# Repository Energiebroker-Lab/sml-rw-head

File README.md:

# sml-rw-head

## Overview

**sml-rw-head** is a versatile read-write module designed to attach to power meters via a magnet.
It reads the SML (Smart Message Language) or ODT stream from the D0 interface of the meter.
Additionally, the device is equipped to send pulses for entering the PIN or navigating through the menu of the meter
and for example toggle the info mode.

This project encompasses three main components:

1. **Hardware:** Includes schematics and PCB (Printed Circuit Board) designs.
2. **3D-Printable Parts:** Consists of printable components that complement the hardware.
3. **Code:** The code is an implementation example
of the sml-rw-head device.

Each major component has its dedicated directory with its own README.md for detailed information.

## Project Structure

- **Hardware:** The hardware files are located in the `./hardware/d0reader` subdirectory. Refer to the [Hardware README](./hardware/d0reader/README.md) for specifics.

- **3D-Printable Parts:** Find 3D-printable files in the `./hardware/3d-print` subdirectory. More details are available in the [3D-Print README](./hardware/3d-print/README.md).

- **Code:** The source code is in the `./code/sml_rw` subdirectory. To get started with the code, please check the [Code README](./code/sml_rw/README.md).

## Usage

Before using the sml-rw-head module, make sure to review the documentation for each component. Follow the guidelines provided in the respective READMEs for successful integration into your project.

### Preparation
Before using the sml-rw-head module, you need to configure the device using the `ftprog_template.xml` file. Import the file and perform the configuration using the [ftprog](https://ftdichip.com/utilities/) software supplied by FTDI.

## Contributions

Contributions to the sml-rw-head project are welcome! If you have ideas, improvements, or bug fixes, please feel free to submit issues or pull requests.

## License

This project is licensed under the [MIT License](LICENSE). See the LICENSE file for more details.

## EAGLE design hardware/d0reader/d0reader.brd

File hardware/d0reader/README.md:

Based on https://www.stefan-weigert.de/php_loader/sml.php

# BOM
| Part | Value           | Device             | Package             | Description                                                             |
|------|-----------------|--------------------|---------------------|-------------------------------------------------------------------------|
| C1   | 100n            | Capacitor          | 0805                | Capacitor, Ceramic                                                      |
| C2   | 100n            | Capacitor          | 0805                | Capacitor, Ceramic                                                      |
| C3   | 100n            | Capacitor          | 0805                | Capacitor, Ceramic                                                      |
| C4   | 1u              | Capacitor          | 0805                | Capacitor, Ceramic                                                      |
| C5   | 1u              | Capacitor          | 0805                | Capacitor, Ceramic                                                      |
| C6   | 22u             | EEEHA1C220R        | CPOL-EU153CLV-0505  | 153CLV-0505 POLARIZED CAPACITOR                                         |
| IC1  | FT232RL         | FT232RL            | SSOP28              | Source: http://www.ftdichip.com/Documents/DataSheets/DS_FT232R_v104.pdf | 
| LED1 | KCL5587S        | LED5MM             | LED5MM              | Infrared-Emitter                                                        |                                                                     
| LED2 | LEDCHIPLED_0805 | CHIPLED            | 0805                | LED (optional)                                                          |                                                                                        
| LED3 | LEDCHIPLED_0805 | CHIPLED            | 0805                | LED (optional)                                                          |                                                                                        
| PAD1 |                 | WIREPADSMD1,27-254 | SMD1,27-2,54        | Wire PAD connect wire on PCB                                            |                                            
| PAD2 |                 | WIREPADSMD1,27-254 | SMD1,27-2,54        | Wire PAD connect wire on PCB                                            |                                        
| PAD3 |                 | WIREPADSMD1,27-254 | SMD1,27-2,54        | Wire PAD connect wire on PCB                                            |                           
| PAD4 |                 | WIREPADSMD1,27-254 | SMD1,27-2,54        | Wire PAD connect wire on PCB                                            |                           
| Q1   | BC817           | BC817-16LT1SMD     | SOT23-BEC           | NPN Transistor                                                          |     NPN Transistor                                                      |                
| Q2   | SFH_309_FA-4/5  | SFH_309_FA-4/5     | XDCR_SFH_309_FA-4/5 | Phototransistor IR Chip Silicon 900nm 2-Pin T-1 Check prices            |
| Q3   | BC817           | BC817-16LT1SMD     | SOT23-BEC           | NPN Transistor                                                          |                                            
| Q4   | BC817           | BC817-16LT1SMD     | SOT23-BEC           | NPN Transistor                                                          |                                           
| R1   | 220             | Resistor           | 0805                | Resistor                                                                |
| R2   | 220             | Resistor           | 0805                | Resistor                                                                |                                     
| R3   | 12k             | Resistor           | 0805                | Resistor                                                                |                                     
| R4   | 12k             | Resistor           | 0805                | Resistor                                                                |                                     
| R5   | 75              | Resistor           | 0805                | Resistor                                                                |                                     
| R6   | 220             | Resistor           | 0805                | Resistor                                                                |                                     
| R7   | 220             | Resistor           | 0805                | Resistor                                                                |                                     
| U4   | SN74LVC1G17DBVR | Schmitt-Trigger    | SOT-23              | Schmitt-Trigger                                                         |

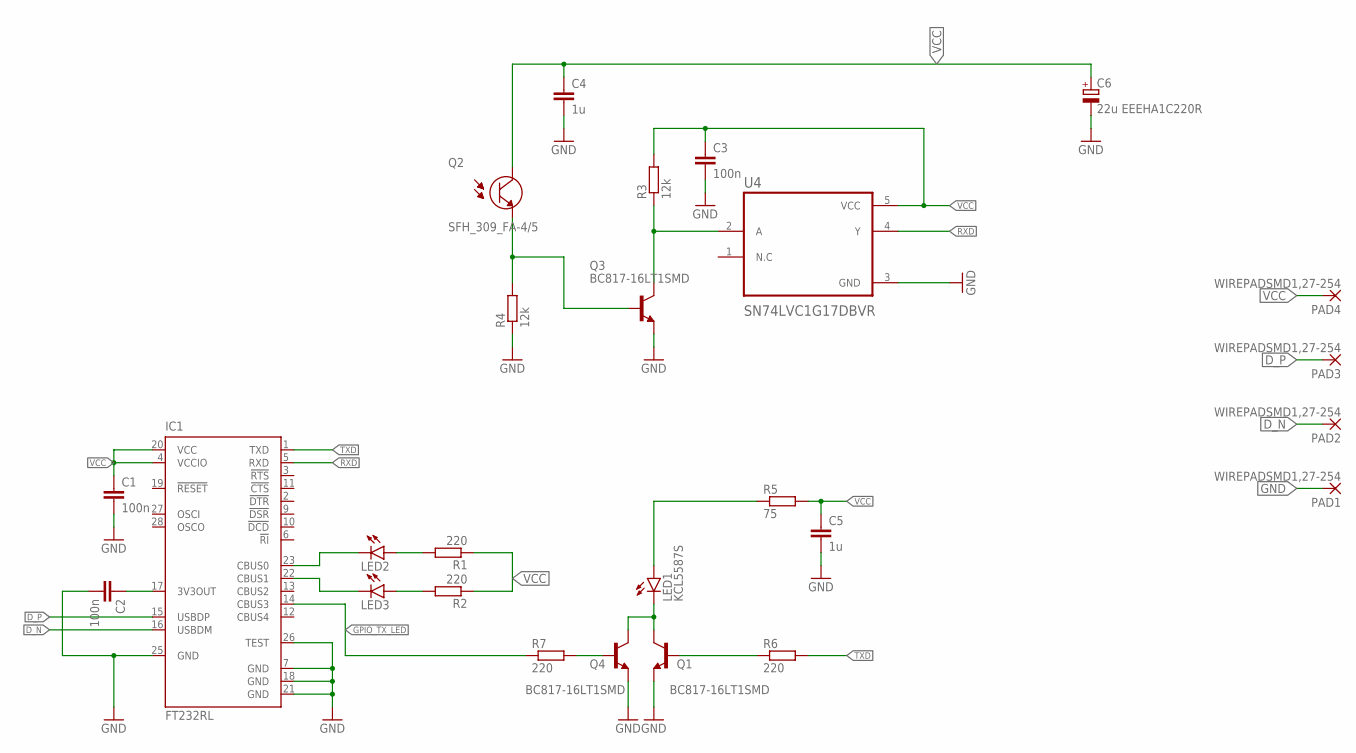
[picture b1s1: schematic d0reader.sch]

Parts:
C1, C2, C3: 100n; C0805
C4, C5: 1u; C0805
C6: 22u EEEHA1C220R; 153CLV-0505
IC1: FT232RL; SSOP28
LED1: KCL5587S; LED5MM
LED2, LED3: LEDCHIPLED_0805; CHIPLED_0805
PAD1, PAD2, PAD3, PAD4: WIREPADSMD1,27-254; SMD1,27-2,54
Q1, Q3, Q4: BC817-16LT1SMD; SOT23-BEC
Q2: SFH_309_FA-4/5; XDCR_SFH_309_FA-4/5
R1, R2, R6, R7: 220; R0805
R3, R4: 12k; R0805
R5: 75; R0805
U4: SN74LVC1G17DBVR; SOT95P280X145-5N

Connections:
D_N: IC1.16 (USBDM), PAD2.1
D_P: IC1.15 (USBDP), PAD3.1
GND: C1.2, C2.2, C3.2, C4.2, C5.2, C6.-, IC1.7 (GND), IC1.18 (GND), IC1.21 (GND), IC1.25 (GND), IC1.26 (TEST), PAD1.1, Q1.E, Q3.E, Q4.E, R4.1, U4.3 (GND)
GPIO_TX_LED: IC1.14 (CBUS3), R7.1
INPUTA: Q3.C, R3.1, U4.2 (A)
unnamed: LED2.A, R1.2
unnamed: LED3.A, R2.2
unnamed: C2.1, IC1.17 (3V3OUT)
OPTO_RX: Q2.1 (E), Q3.B, R4.2
RXD: IC1.5 (RXD), U4.4 (Y)
RXLED: IC1.22 (CBUS1), LED3.C
TXD: IC1.1 (TXD), R6.2
TXLED: IC1.23 (CBUS0), LED2.C
TXLEDGND: LED1.K (C), Q1.C, Q4.C
TXLEDVCC: LED1.A, R5.1
TX_LED_Q1: Q1.B, R6.1
TX_LED_Q4: Q4.B, R7.2
VCC: C1.1, C3.1, C4.1, C5.1, C6.+, IC1.4 (VCCIO), IC1.20 (VCC), PAD4.1, Q2.2 (C), R1.1, R2.1, R3.2, R5.2, U4.5 (VCC)

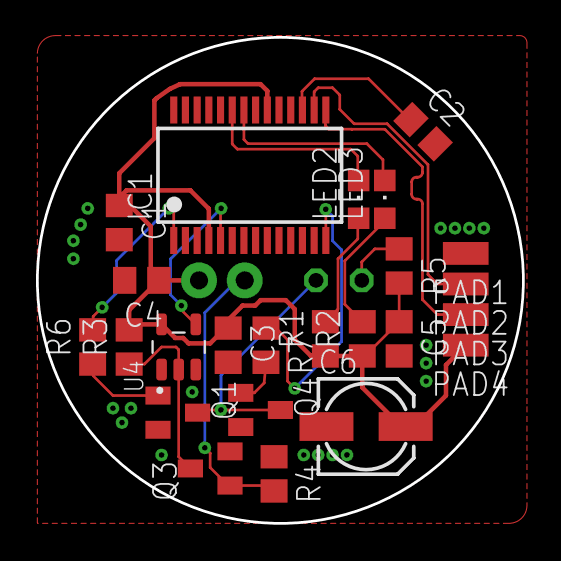
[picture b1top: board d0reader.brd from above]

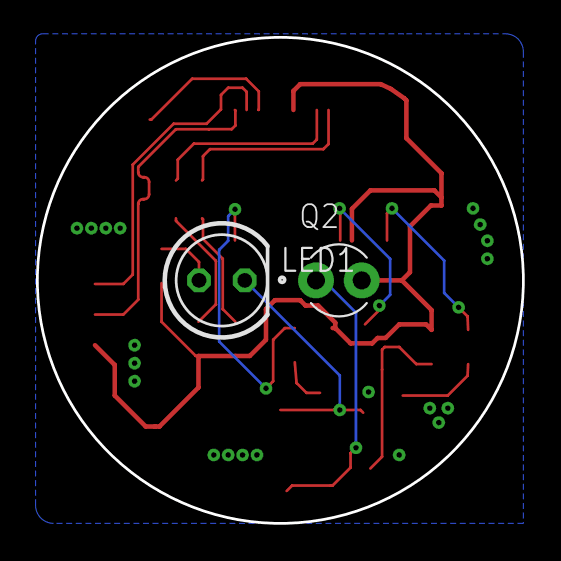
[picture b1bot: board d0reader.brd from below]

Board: 2 copper layers, 27.0 x 27.0 mm, 26 parts (2 on the bottom side), 18 nets.

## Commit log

2023-12-19 adds hardware
2023-12-19 updates .gitignore
2023-12-21 adds git action workflow pylint, mypy
2023-12-21 code push
2023-12-21 updates pylint git action workflow
2023-12-21 updates mypy git action workflow
2023-12-21 adds pylintrc
2023-12-21 updates pylintrc encoding
2023-12-21 updates pylintrc
2023-12-22 adds dd3 odt and 2way
2023-12-22 adds reattach pre port open
2023-12-22 adds odt logic
2023-12-22 adds README.md
2023-12-22 example code
    code push
2024-01-02 adds easy meter handler
2024-01-02 updates README.md for the code
2024-01-02 updates README.md for depth stencil
2024-01-02 updates README.md for hardware
2024-01-02 Create LICENSE
2024-01-02 updates README.md for project
2024-01-02 adds ftprog template
2024-01-02 adds image to README.md
2024-01-02 Bump actions/setup-python from 2 to 5
    Bumps [actions/setup-python](https://github.com/actions/setup-python) from 2 to 5.
    - [Release notes](https://github.com/actions/setup-python/releases)
    - [Commits](https://github.com/actions/setup-python/compare/v2...v5)
    ---
    updated-dependencies:
    - dependency-name: actions/setup-python
2024-01-02 Bump actions/checkout from 2 to 4
    Bumps [actions/checkout](https://github.com/actions/checkout) from 2 to 4.
    - [Release notes](https://github.com/actions/checkout/releases)
    - [Changelog](https://github.com/actions/checkout/blob/main/CHANGELOG.md)
    - [Commits](https://github.com/actions/checkout/compare/v2...v4)
    ---
    updated-dependencies:
2024-01-02 removes wrong name from README.md
2024-04-01 Bump fire from 0.5.0 to 0.6.0 in /code/sml_rw
    Bumps [fire](https://github.com/google/python-fire) from 0.5.0 to 0.6.0.
    - [Release notes](https://github.com/google/python-fire/releases)
    - [Commits](https://github.com/google/python-fire/compare/v0.5.0...v0.6.0)
    ---
    updated-dependencies:
    - dependency-name: fire
2024-05-01 Bump smllib from 1.3 to 1.4 in /code/sml_rw
    Bumps [smllib](https://github.com/spacemanspiff2007/SmlLib) from 1.3 to 1.4.
    - [Release notes](https://github.com/spacemanspiff2007/SmlLib/releases)
    - [Commits](https://github.com/spacemanspiff2007/SmlLib/compare/1.3...1.4)
    ---
    updated-dependencies:
    - dependency-name: smllib
2024-05-01 Bump pyftdi from 0.55.0 to 0.55.4 in /code/sml_rw
    Bumps [pyftdi](https://github.com/eblot/pyftdi) from 0.55.0 to 0.55.4.
    - [Commits](https://github.com/eblot/pyftdi/compare/v0.55.0...v0.55.4)
    ---
    updated-dependencies:
    - dependency-name: pyftdi
    dependency-type: direct:production
